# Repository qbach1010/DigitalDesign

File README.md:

## Digital Design Project

## 📝 Project Overview

Design a 3-bit signed (X) to 3-bit signed (Y) computer, which includes operations: add, subtract, multiply, and XOR. The user can select X, Y, and the operation to compute via physical switches. 

*   **EDA Tool:** KiCad 10.0
  
*   **Dimensions:** 120 x 180 mm
  
*   **Layer Count:** 2 layers
  
*   **Primary Logic:** Computes directly through discrete logic gates: AND (CD4081), OR (CD4071), and NOT (74HC04).
  
*   **Libraries Used:** Standard KiCad library.

### 📸 Schematics & Layout

---

## 🛠️ Key Hardware Features
The main functional blocks of the schematic include:

*   **Power Supply:** Uses a 7805 voltage regulator to accept 7 ~ 14 VDC, or just using 5VDC pin to power up the circuit and provide the logic HIGH.
  
*   **Adder:** A simple 3-bit to 3-bit adder using full adders.
  
*   **Two's Complement:** Changes the sign of the 3-bit number, utilizing the adder block to also perform subtraction.
  
*   **Multiplier:** Uses **Baugh-Wooley multiplication** for multiplying the signed 3-bit numbers.
  
*   **Sign Extend:** Due to the difference between the output of the multiply operation (6 bits) and all other operations (3 bits), sign-extension logic is added to make all final outputs a uniform 6 bits wide.

---

## 🔍 Editing the Design
To view or modify the hardware files:

1. Clone this repository to your local machine.

2. Open the main `.kicad_pro` project file in **KiCad 10.0**.

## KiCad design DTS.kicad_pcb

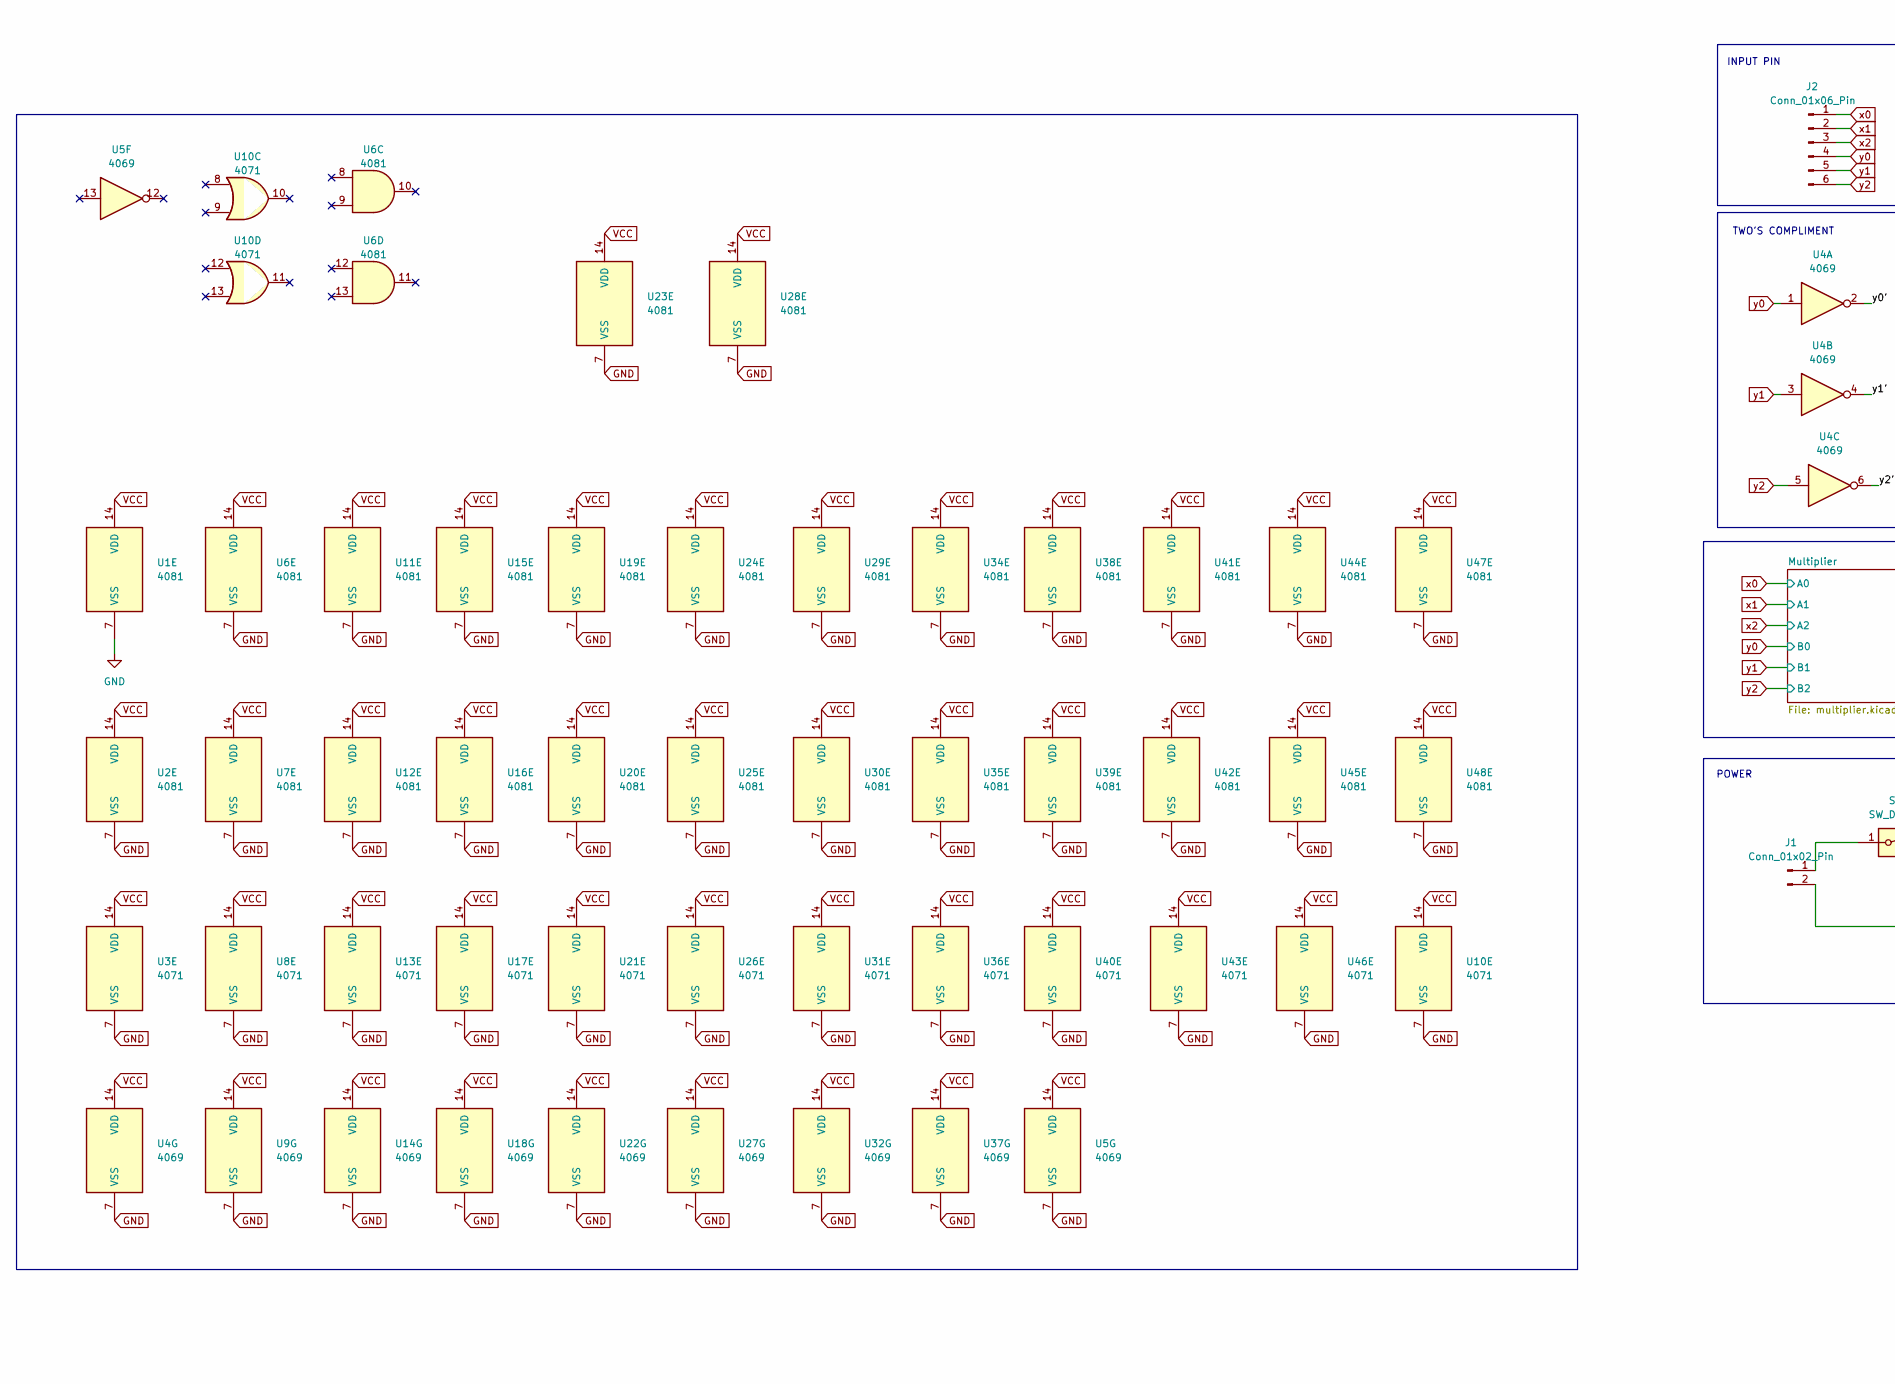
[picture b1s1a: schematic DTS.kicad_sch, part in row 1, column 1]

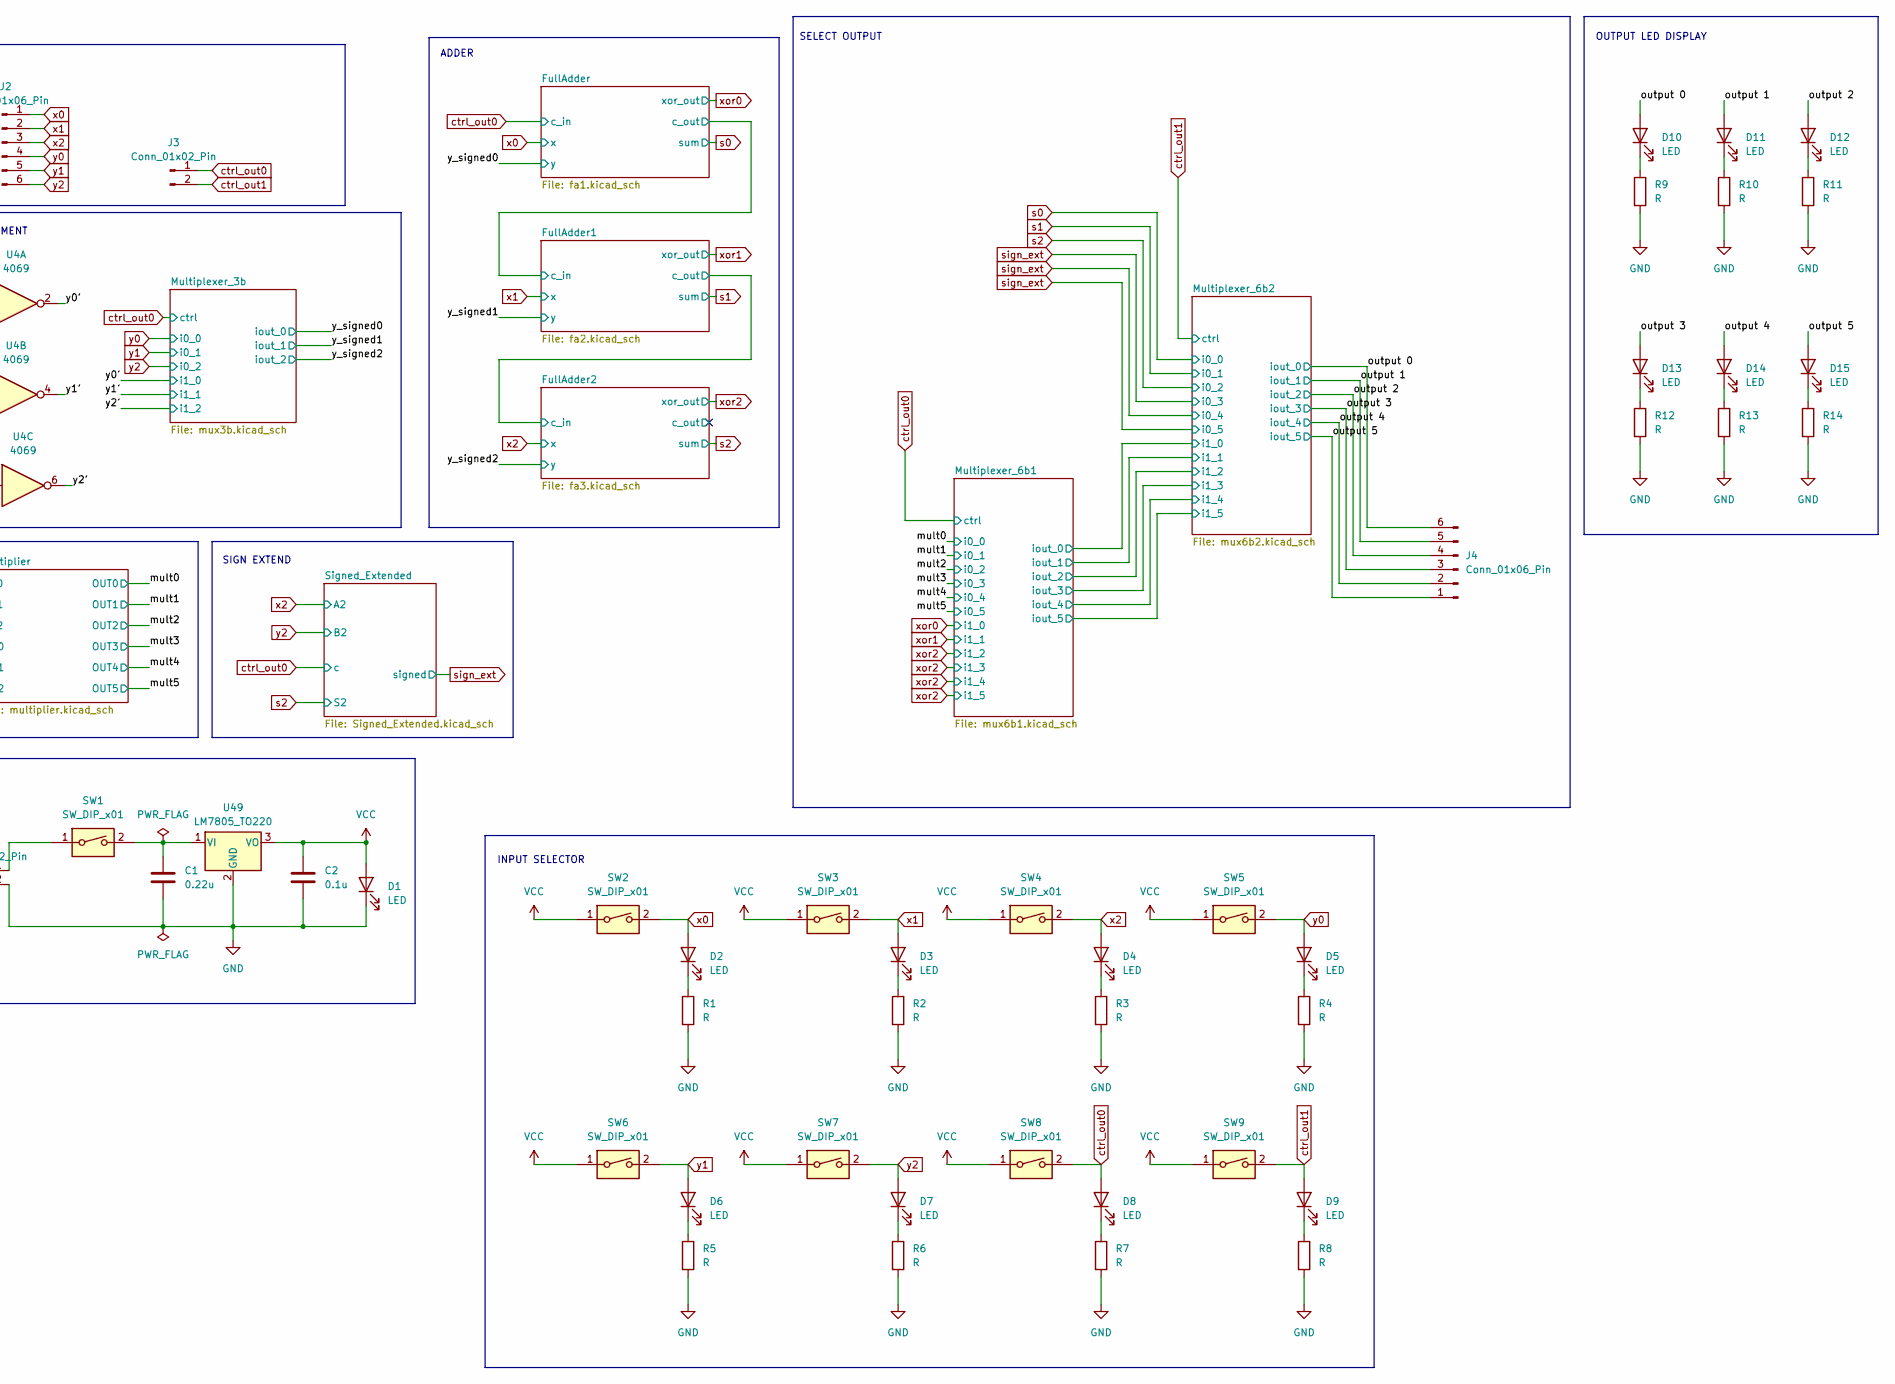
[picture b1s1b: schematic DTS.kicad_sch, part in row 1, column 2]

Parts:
C1: 0.22u; C_Radial_D6.3mm_H5.0mm_P2.50mm
C2: 0.1u; C_Radial_D6.3mm_H5.0mm_P2.50mm
D1, D2, D3, D4, D5, D6, D7, D8, D9, D10, D11, D12, D13, D14, D15: LED; PinHeader_1x02_P2.54mm_Vertical
J1, J3: Conn_01x02_Pin; PinHeader_1x02_P2.54mm_Vertical
J2, J4: Conn_01x06_Pin; PinHeader_1x06_P2.54mm_Vertical
R1, R2, R3, R4, R5, R6, R7, R8, R9, R10, R11, R12, R13, R14: R; PinHeader_1x02_P2.54mm_Vertical
SW1, SW2, SW3, SW4, SW5, SW6, SW7, SW8, SW9: SW_DIP_x01; PinHeader_1x03_P2.54mm_Vertical
U1, U2, U6, U7, U11, U12, U15, U16, U19, U20, U23, U24, U25, U28, U29, U30, U34, U35, U38, U39, U41, U42, U44, U45, U47, U48: 4081; CERDIP-14_W7.62mm_SideBrazed_LongPads_Socket
U3, U8, U10, U13, U17, U21, U26, U31, U36, U40, U43, U46: 4071; CERDIP-14_W7.62mm_SideBrazed_LongPads_Socket
U4, U5, U9, U14, U18, U22, U27, U32, U37: 4069; CERDIP-14_W7.62mm_SideBrazed_LongPads_Socket
U49: LM7805_TO220; TO-220-3_Vertical

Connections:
/output 0: D10.2 (A), J4.6; also elsewhere on the board
/output 1: D11.2 (A), J4.5; also elsewhere on the board
/output 2: D12.2 (A), J4.4; also elsewhere on the board
/output 3: D13.2 (A), J4.3; also elsewhere on the board
/output 4: D14.2 (A), J4.2; also elsewhere on the board
/output 5: D15.2 (A), J4.1; also elsewhere on the board
/y0': U4.2; also elsewhere on the board
/y1': U4.4; also elsewhere on the board
/y2': U4.6; also elsewhere on the board
GND: C1.2, C2.2, D1.1 (K), J1.2, R1.2, R2.2, R3.2, R4.2, R5.2, R6.2, R7.2, R8.2, R9.2, R10.2, R11.2, R12.2, R13.2, R14.2, U1.7 (VSS), U2.7 (VSS), U3.7 (VSS), U4.7 (VSS), U5.7 (VSS), U6.7 (VSS), U7.7 (VSS), U8.7 (VSS), U9.7 (VSS), U10.7 (VSS), U11.7 (VSS), U12.7 (VSS), U13.7 (VSS), U14.7 (VSS), U15.7 (VSS), U16.7 (VSS), U17.7 (VSS), U18.7 (VSS), U19.7 (VSS), U20.7 (VSS), U21.7 (VSS), U22.7 (VSS), U23.7 (VSS), U24.7 (VSS), U25.7 (VSS), U26.7 (VSS), U27.7 (VSS), U28.7 (VSS), U29.7 (VSS), U30.7 (VSS), U31.7 (VSS), U32.7 (VSS), U34.7 (VSS), U35.7 (VSS), U36.7 (VSS), U37.7 (VSS), U38.7 (VSS), U39.7 (VSS), U40.7 (VSS), U41.7 (VSS), U42.7 (VSS), U43.7 (VSS), U44.7 (VSS), U45.7 (VSS), U46.7 (VSS), U47.7 (VSS), U48.7 (VSS), U49.2 (GND); also elsewhere on the board
unnamed: D2.1 (K), R1.1
unnamed: D3.1 (K), R2.1
unnamed: D4.1 (K), R3.1
unnamed: D5.1 (K), R4.1
unnamed: D6.1 (K), R5.1
unnamed: D7.1 (K), R6.1
unnamed: D8.1 (K), R7.1
unnamed: D9.1 (K), R8.1
unnamed: D10.1 (K), R9.1
unnamed: D11.1 (K), R10.1
unnamed: D12.1 (K), R11.1
unnamed: D13.1 (K), R12.1
unnamed: D14.1 (K), R13.1
unnamed: D15.1 (K), R14.1
unnamed: J1.1, SW1.1
unnamed: C1.1, SW1.2, U49.1 (VI)
VCC: C2.1, D1.2 (A), SW2.1, SW3.1, SW4.1, SW5.1, SW6.1, SW7.1, SW8.1, SW9.1, U1.14 (VDD), U2.14 (VDD), U3.14 (VDD), U4.14 (VDD), U5.14 (VDD), U6.14 (VDD), U7.14 (VDD), U8.14 (VDD), U9.14 (VDD), U10.14 (VDD), U11.14 (VDD), U12.14 (VDD), U13.14 (VDD), U14.14 (VDD), U15.14 (VDD), U16.14 (VDD), U17.14 (VDD), U18.14 (VDD), U19.14 (VDD), U20.14 (VDD), U21.14 (VDD), U22.14 (VDD), U23.14 (VDD), U24.14 (VDD), U25.14 (VDD), U26.14 (VDD), U27.14 (VDD), U28.14 (VDD), U29.14 (VDD), U30.14 (VDD), U31.14 (VDD), U32.14 (VDD), U34.14 (VDD), U35.14 (VDD), U36.14 (VDD), U37.14 (VDD), U38.14 (VDD), U39.14 (VDD), U40.14 (VDD), U41.14 (VDD), U42.14 (VDD), U43.14 (VDD), U44.14 (VDD), U45.14 (VDD), U46.14 (VDD), U47.14 (VDD), U48.14 (VDD), U49.3 (VO); also elsewhere on the board
ctrl_out0: D8.2 (A), J3.1, SW8.2; also elsewhere on the board
ctrl_out1: D9.2 (A), J3.2, SW9.2; also elsewhere on the board
x0: D2.2 (A), J2.1, SW2.2; also elsewhere on the board
x1: D3.2 (A), J2.2, SW3.2; also elsewhere on the board
x2: D4.2 (A), J2.3, SW4.2; also elsewhere on the board
y0: D5.2 (A), J2.4, SW5.2, U4.1; also elsewhere on the board
y1: D6.2 (A), J2.5, SW6.2, U4.3; also elsewhere on the board
y2: D7.2 (A), J2.6, SW7.2, U4.5; also elsewhere on the board

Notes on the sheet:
ADDER
INPUT PIN
SIGN EXTEND
POWER
SELECT OUTPUT
OUTPUT LED DISPLAY
TWO'S COMPLIMENT
INPUT SELECTOR

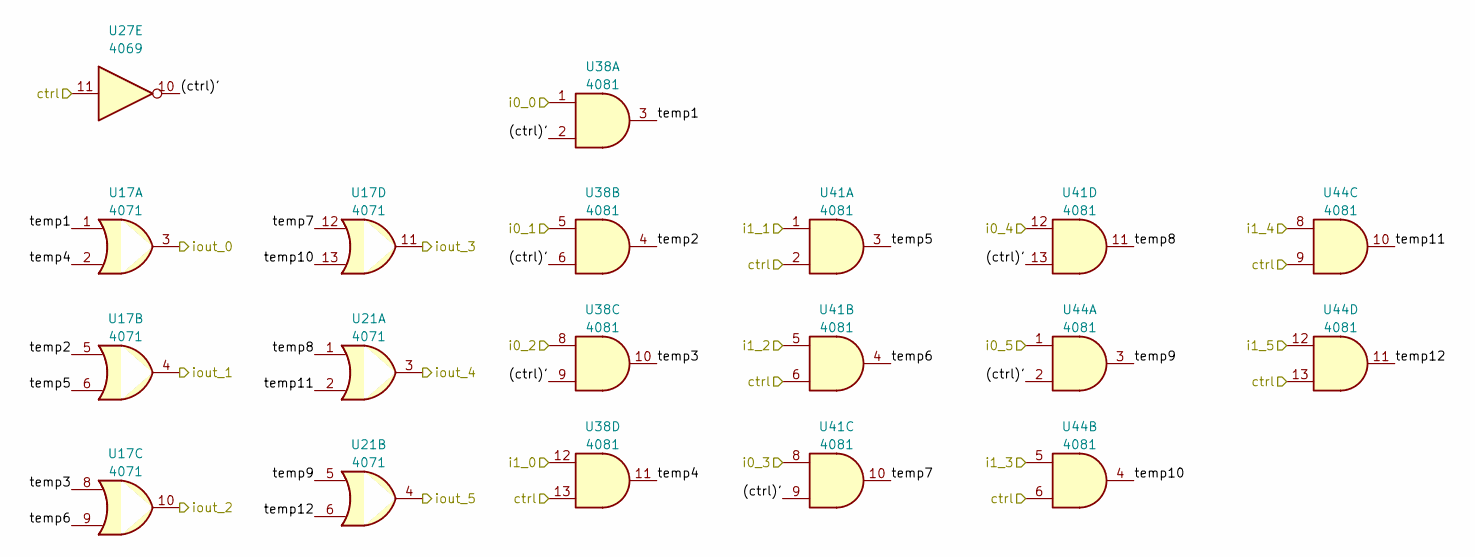
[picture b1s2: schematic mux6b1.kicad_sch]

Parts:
U17, U21: 4071; CERDIP-14_W7.62mm_SideBrazed_LongPads_Socket
U27: 4069; CERDIP-14_W7.62mm_SideBrazed_LongPads_Socket
U38, U41, U44: 4081; CERDIP-14_W7.62mm_SideBrazed_LongPads_Socket

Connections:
/Multiplexer_6b1/(ctrl)': U27.10, U38.2, U38.6, U38.9, U41.9, U41.13, U44.2
/Multiplexer_6b1/iout_0: U17.3; also elsewhere on the board
/Multiplexer_6b1/iout_1: U17.4; also elsewhere on the board
/Multiplexer_6b1/iout_2: U17.10; also elsewhere on the board
/Multiplexer_6b1/iout_3: U17.11; also elsewhere on the board
/Multiplexer_6b1/iout_4: U21.3; also elsewhere on the board
/Multiplexer_6b1/iout_5: U21.4; also elsewhere on the board
/Multiplexer_6b1/temp1: U17.1, U38.3
/Multiplexer_6b1/temp2: U17.5, U38.4
/Multiplexer_6b1/temp3: U17.8, U38.10
/Multiplexer_6b1/temp4: U17.2, U38.11
/Multiplexer_6b1/temp5: U17.6, U41.3
/Multiplexer_6b1/temp6: U17.9, U41.4
/Multiplexer_6b1/temp7: U17.12, U41.10
/Multiplexer_6b1/temp8: U21.1, U41.11
/Multiplexer_6b1/temp9: U21.5, U44.3
/Multiplexer_6b1/temp10: U17.13, U44.4
/Multiplexer_6b1/temp11: U21.2, U44.10
/Multiplexer_6b1/temp12: U21.6, U44.11
/mult0: U38.1; also elsewhere on the board
/mult1: U38.5; also elsewhere on the board
/mult2: U38.8; also elsewhere on the board
/mult3: U41.8; also elsewhere on the board
/mult4: U41.12; also elsewhere on the board
/mult5: U44.1; also elsewhere on the board
ctrl_out0: U27.11, U38.13, U41.2, U41.6, U44.6, U44.9, U44.13; also elsewhere on the board
xor0: U38.12; also elsewhere on the board
xor1: U41.1; also elsewhere on the board
xor2: U41.5, U44.5, U44.8, U44.12; also elsewhere on the board

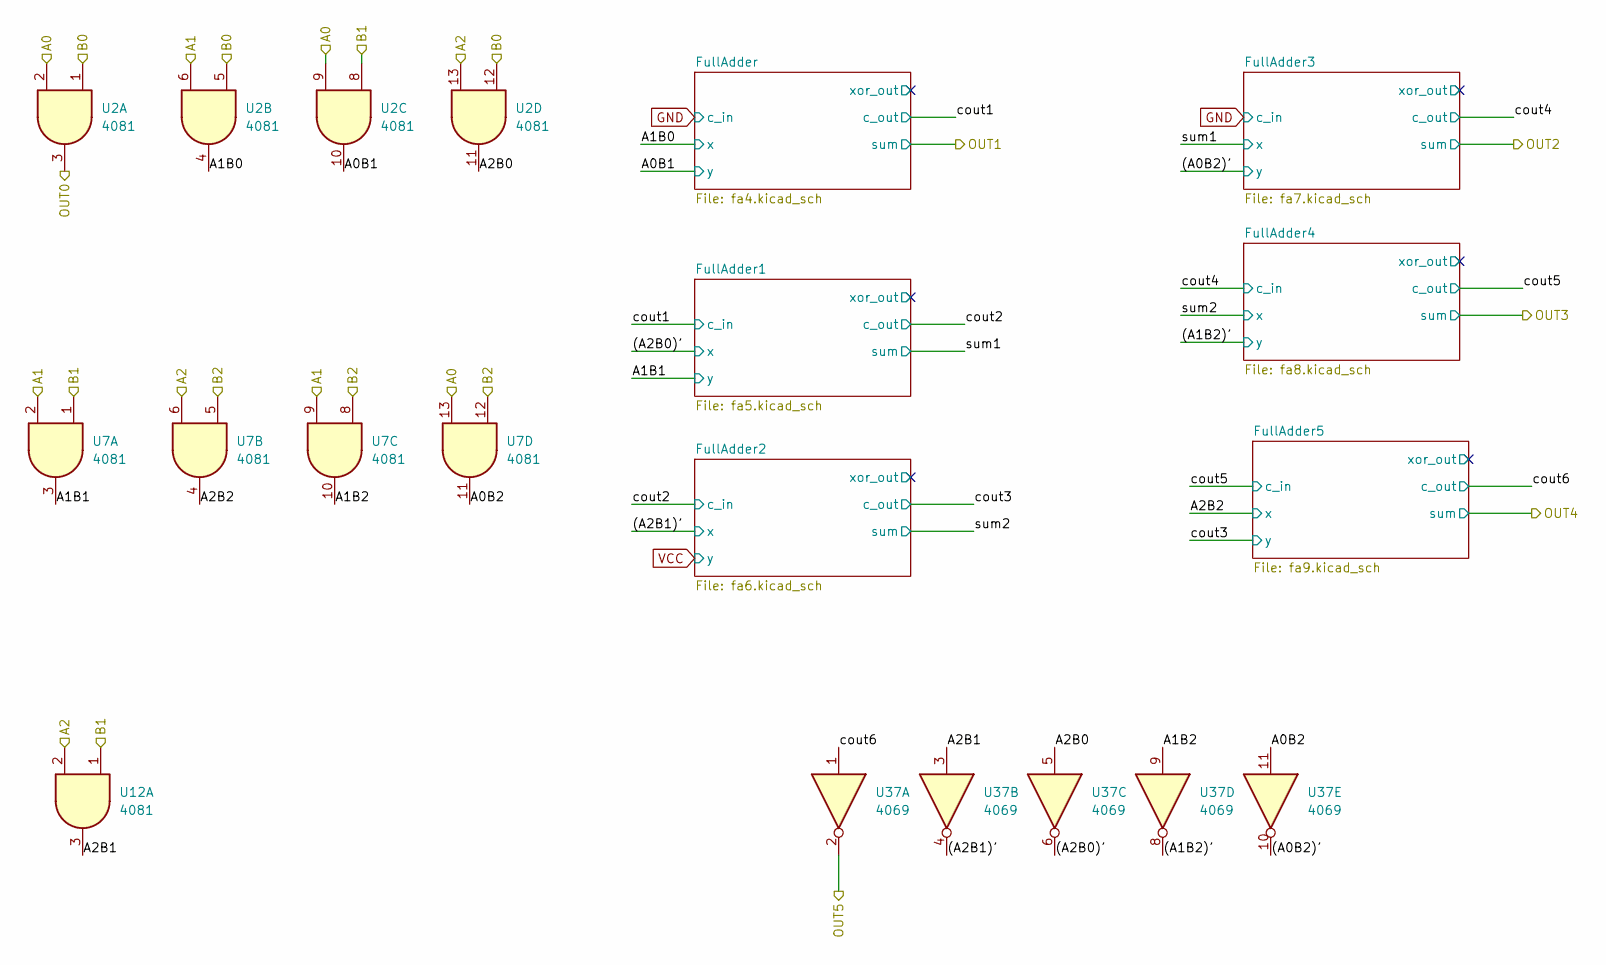
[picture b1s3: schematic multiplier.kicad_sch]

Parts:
U2, U7, U12: 4081; CERDIP-14_W7.62mm_SideBrazed_LongPads_Socket
U37: 4069; CERDIP-14_W7.62mm_SideBrazed_LongPads_Socket

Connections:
/Multiplier/(A0B2)': U37.10; also elsewhere on the board
/Multiplier/(A1B2)': U37.8; also elsewhere on the board
/Multiplier/(A2B0)': U37.6; also elsewhere on the board
/Multiplier/(A2B1)': U37.4; also elsewhere on the board
/Multiplier/A0B1: U2.10; also elsewhere on the board
/Multiplier/A0B2: U7.11, U37.11
/Multiplier/A1B0: U2.4; also elsewhere on the board
/Multiplier/A1B1: U7.3; also elsewhere on the board
/Multiplier/A1B2: U7.10, U37.9
/Multiplier/A2B0: U2.11, U37.5
/Multiplier/A2B1: U12.3, U37.3
/Multiplier/A2B2: U7.4; also elsewhere on the board
/Multiplier/cout6: U37.1; also elsewhere on the board
/mult0: U2.3; also elsewhere on the board
/mult5: U37.2; also elsewhere on the board
x0: U2.2, U2.9, U7.13; also elsewhere on the board
x1: U2.6, U7.2, U7.9; also elsewhere on the board
x2: U2.13, U7.6, U12.2; also elsewhere on the board
y0: U2.1, U2.5, U2.12; also elsewhere on the board
y1: U2.8, U7.1, U12.1; also elsewhere on the board
y2: U7.5, U7.8, U7.12; also elsewhere on the board

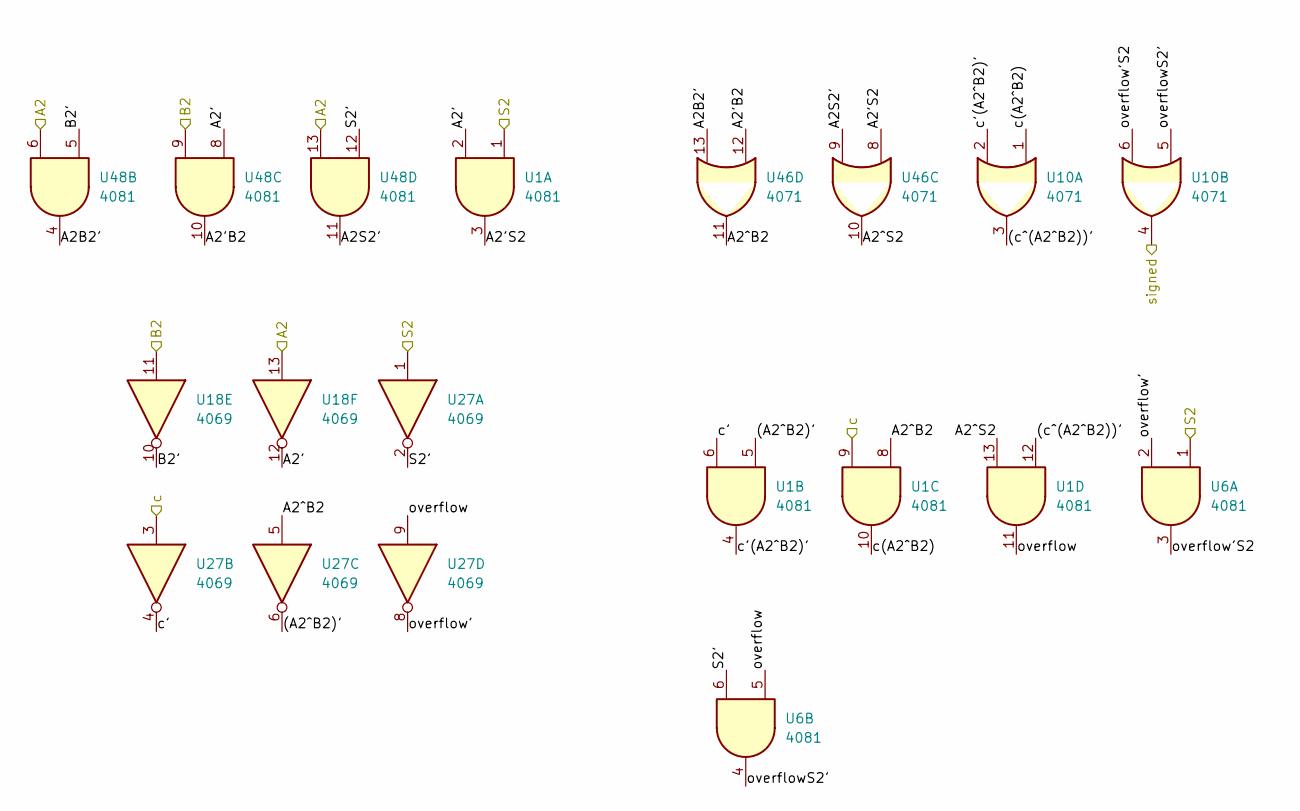
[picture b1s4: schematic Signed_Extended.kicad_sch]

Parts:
U1, U6, U48: 4081; CERDIP-14_W7.62mm_SideBrazed_LongPads_Socket
U10, U46: 4071; CERDIP-14_W7.62mm_SideBrazed_LongPads_Socket
U18, U27: 4069; CERDIP-14_W7.62mm_SideBrazed_LongPads_Socket

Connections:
/Signed_Extended/(A2^B2)': U1.5, U27.6
/Signed_Extended/(c^(A2^B2))': U1.12, U10.3
/Signed_Extended/A2': U1.2, U18.12, U48.8
/Signed_Extended/A2'B2: U46.12, U48.10
/Signed_Extended/A2'S2: U1.3, U46.8
/Signed_Extended/A2B2': U46.13, U48.4
/Signed_Extended/A2S2': U46.9, U48.11
/Signed_Extended/A2^B2: U1.8, U27.5, U46.11
/Signed_Extended/A2^S2: U1.13, U46.10
/Signed_Extended/B2': U18.10, U48.5
/Signed_Extended/S2': U6.6, U27.2, U48.12
/Signed_Extended/c': U1.6, U27.4
/Signed_Extended/c'(A2^B2)': U1.4, U10.2
/Signed_Extended/c(A2^B2): U1.10, U10.1
/Signed_Extended/overflow: U1.11, U6.5, U27.9
/Signed_Extended/overflow': U6.2, U27.8
/Signed_Extended/overflow'S2: U6.3, U10.6
/Signed_Extended/overflowS2': U6.4, U10.5
ctrl_out0: U1.9, U27.3; also elsewhere on the board
s2: U1.1, U6.1, U27.1; also elsewhere on the board
sign_ext: U10.4; also elsewhere on the board
x2: U18.13, U48.6, U48.13; also elsewhere on the board
y2: U18.11, U48.9; also elsewhere on the board

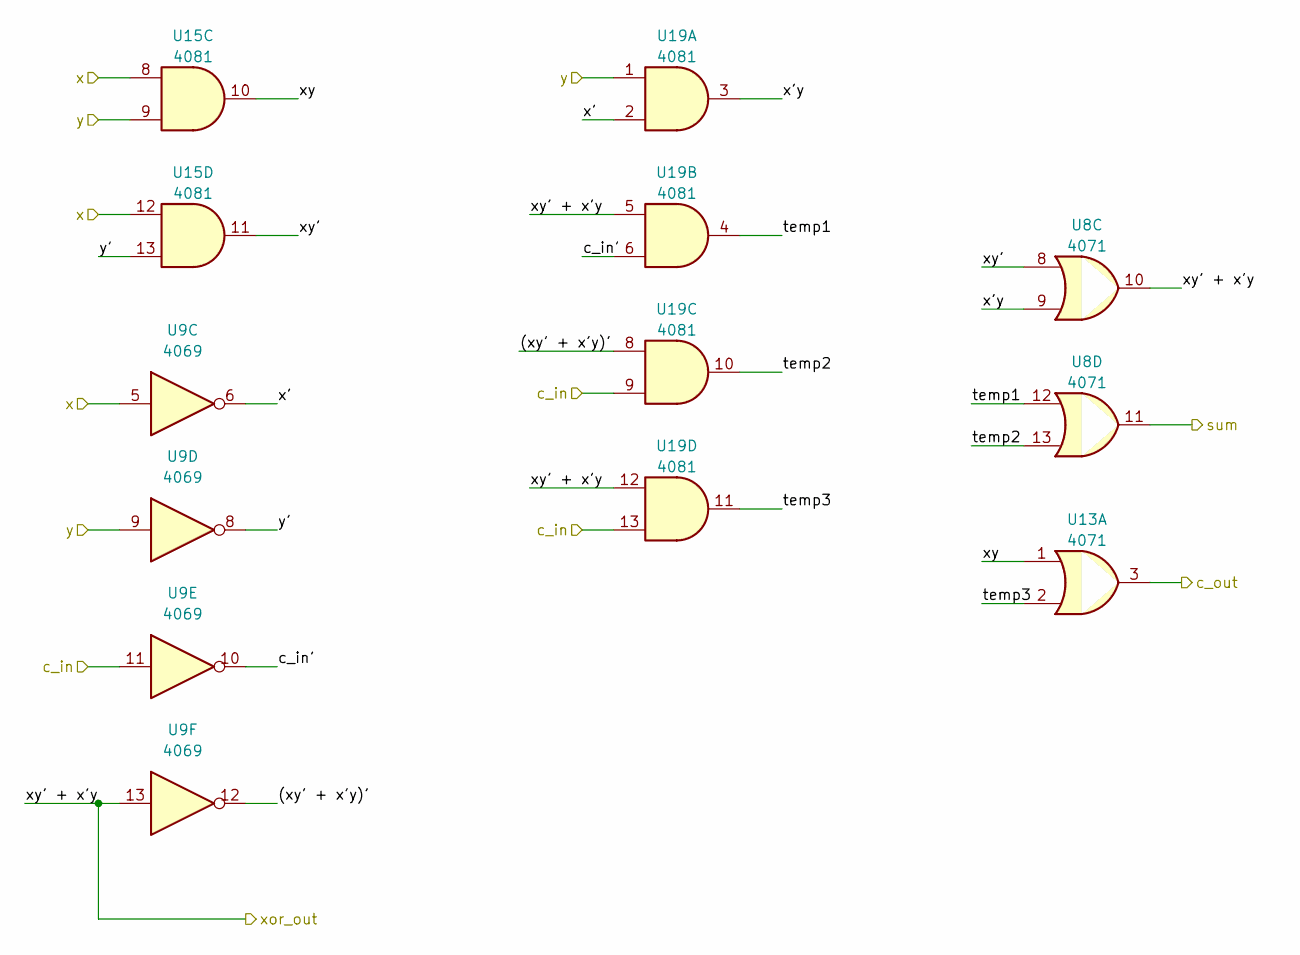
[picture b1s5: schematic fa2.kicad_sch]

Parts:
U8, U13: 4071; CERDIP-14_W7.62mm_SideBrazed_LongPads_Socket
U9: 4069; CERDIP-14_W7.62mm_SideBrazed_LongPads_Socket
U15, U19: 4081; CERDIP-14_W7.62mm_SideBrazed_LongPads_Socket

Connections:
/FullAdder1/(xy' + x'y)': U9.12, U19.8
/FullAdder1/c_in': U9.10, U19.6
/FullAdder1/c_out: U13.3; also elsewhere on the board
/FullAdder1/temp1: U8.12, U19.4
/FullAdder1/temp2: U8.13, U19.10
/FullAdder1/temp3: U13.2, U19.11
/FullAdder1/x': U9.6, U19.2
/FullAdder1/x'y: U8.9, U19.3
/FullAdder1/xy: U13.1, U15.10
/FullAdder1/xy': U8.8, U15.11
/FullAdder1/y': U9.8, U15.13
/FullAdder/c_out: U9.11, U19.9, U19.13; also elsewhere on the board
/y_signed1: U9.9, U15.9, U19.1; also elsewhere on the board
s1: U8.11; also elsewhere on the board
x1: U9.5, U15.8, U15.12; also elsewhere on the board
xor1: U8.10, U9.13, U19.5, U19.12; also elsewhere on the board

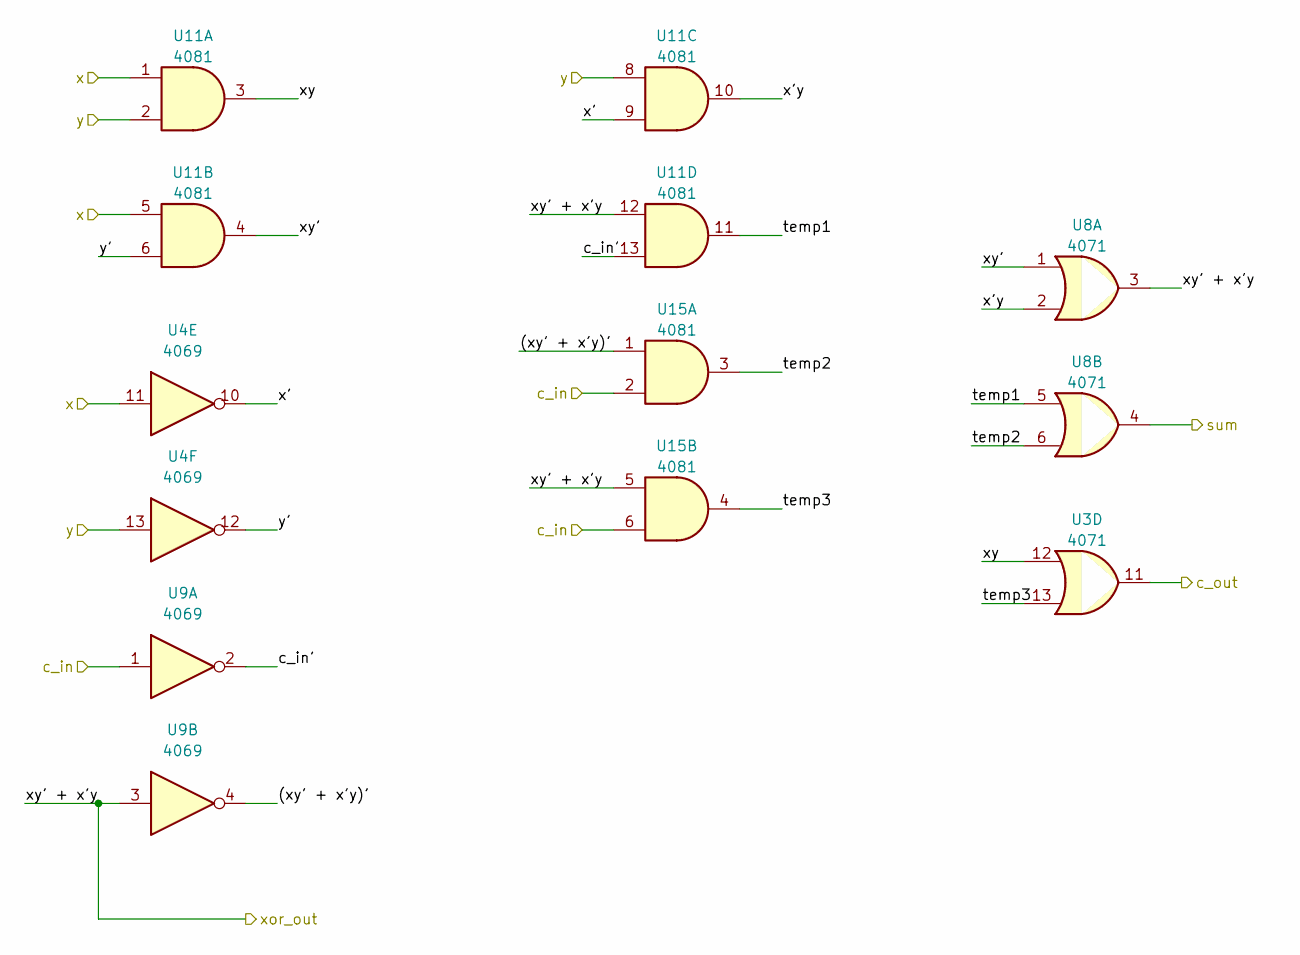
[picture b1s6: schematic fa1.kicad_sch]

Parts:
U3, U8: 4071; CERDIP-14_W7.62mm_SideBrazed_LongPads_Socket
U4, U9: 4069; CERDIP-14_W7.62mm_SideBrazed_LongPads_Socket
U11, U15: 4081; CERDIP-14_W7.62mm_SideBrazed_LongPads_Socket

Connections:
/FullAdder/(xy' + x'y)': U9.4, U15.1
/FullAdder/c_in': U9.2, U11.13
/FullAdder/c_out: U3.11; also elsewhere on the board
/FullAdder/temp1: U8.5, U11.11
/FullAdder/temp2: U8.6, U15.3
/FullAdder/temp3: U3.13, U15.4
/FullAdder/x': U4.10, U11.9
/FullAdder/x'y: U8.2, U11.10
/FullAdder/xy: U3.12, U11.3
/FullAdder/xy': U8.1, U11.4
/FullAdder/y': U4.12, U11.6
/y_signed0: U4.13, U11.2, U11.8; also elsewhere on the board
ctrl_out0: U9.1, U15.2, U15.6; also elsewhere on the board
s0: U8.4; also elsewhere on the board
x0: U4.11, U11.1, U11.5; also elsewhere on the board
xor0: U8.3, U9.3, U11.12, U15.5; also elsewhere on the board

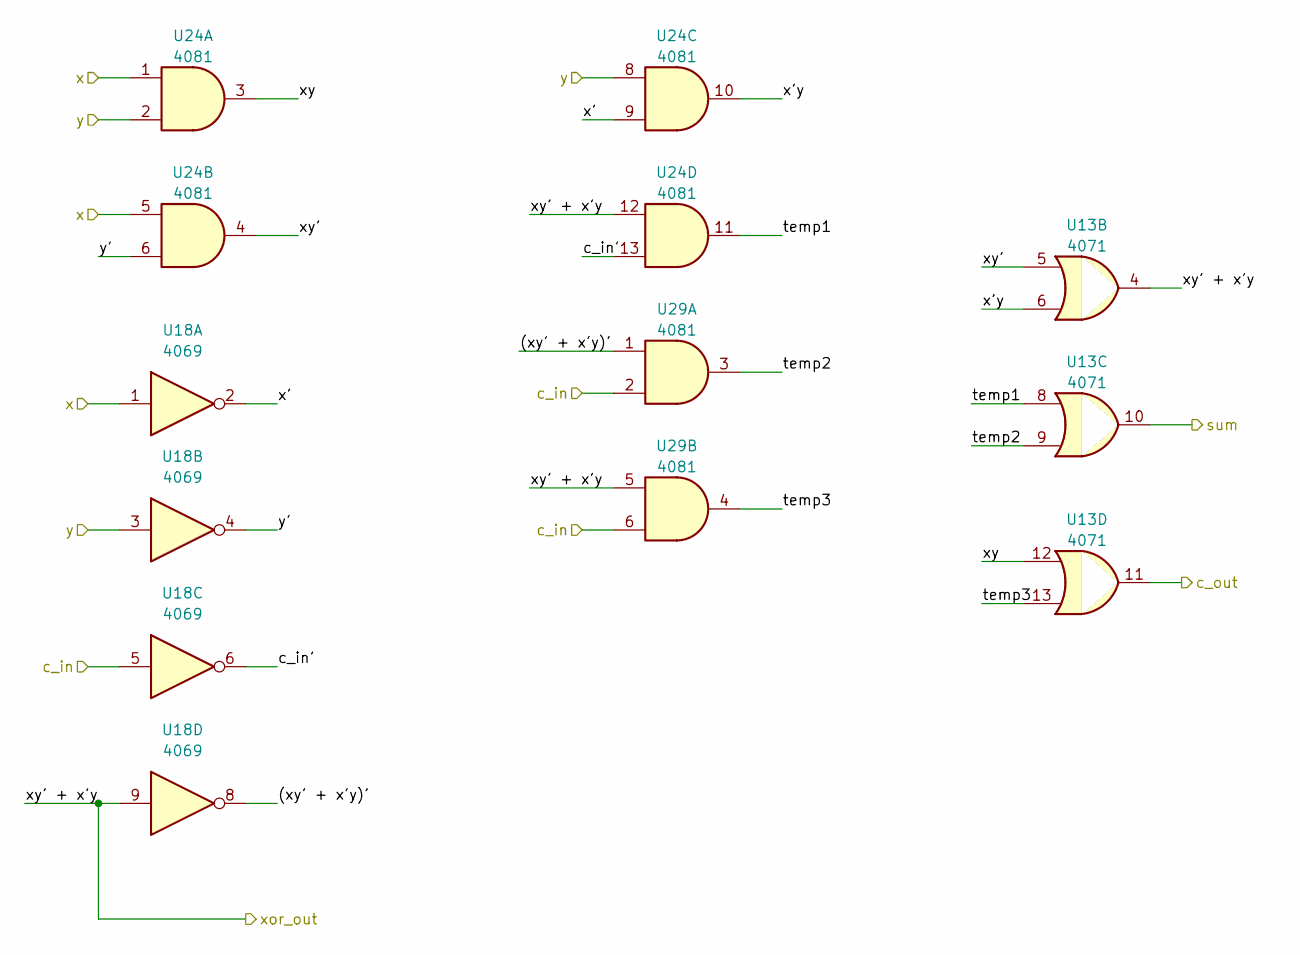
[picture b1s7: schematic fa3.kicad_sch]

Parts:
U13: 4071; CERDIP-14_W7.62mm_SideBrazed_LongPads_Socket
U18: 4069; CERDIP-14_W7.62mm_SideBrazed_LongPads_Socket
U24, U29: 4081; CERDIP-14_W7.62mm_SideBrazed_LongPads_Socket

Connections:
/FullAdder1/c_out: U18.5, U29.2, U29.6; also elsewhere on the board
/FullAdder2/(xy' + x'y)': U18.8, U29.1
/FullAdder2/c_in': U18.6, U24.13
/FullAdder2/c_out: U13.11
/FullAdder2/temp1: U13.8, U24.11
/FullAdder2/temp2: U13.9, U29.3
/FullAdder2/temp3: U13.13, U29.4
/FullAdder2/x': U18.2, U24.9
/FullAdder2/x'y: U13.6, U24.10
/FullAdder2/xy: U13.12, U24.3
/FullAdder2/xy': U13.5, U24.4
/FullAdder2/y': U18.4, U24.6
/y_signed2: U18.3, U24.2, U24.8; also elsewhere on the board
s2: U13.10; also elsewhere on the board
x2: U18.1, U24.1, U24.5; also elsewhere on the board
xor2: U13.4, U18.9, U24.12, U29.5; also elsewhere on the board

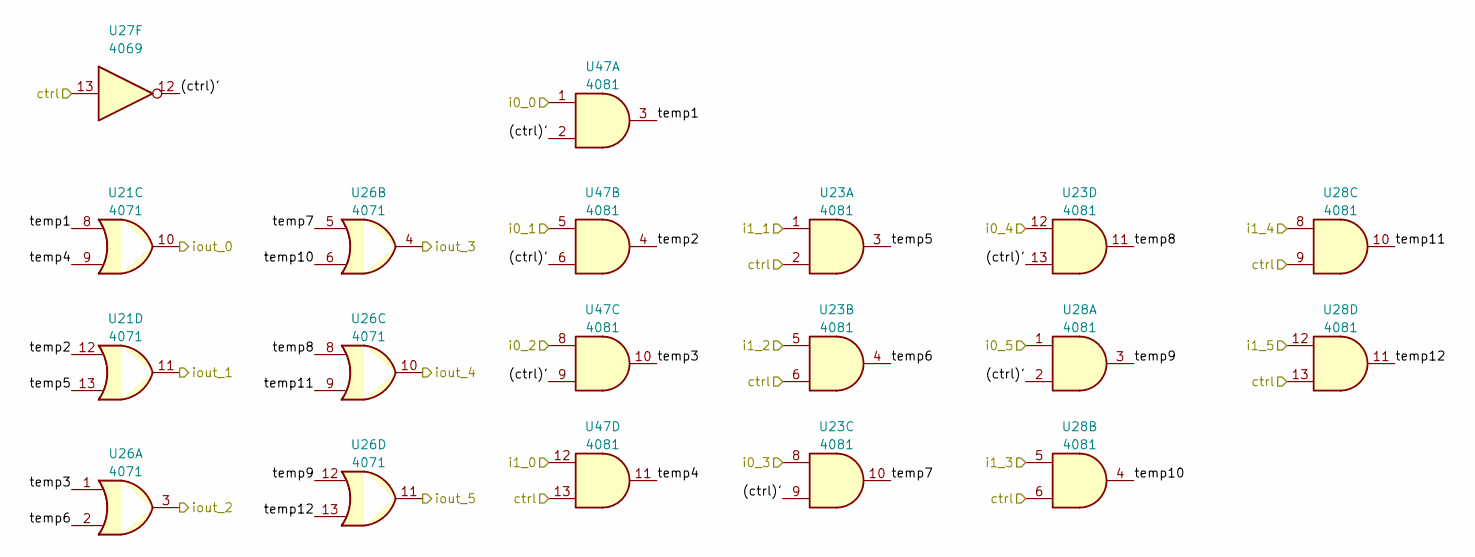
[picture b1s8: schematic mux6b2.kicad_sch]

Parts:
U21, U26: 4071; CERDIP-14_W7.62mm_SideBrazed_LongPads_Socket
U23, U28, U47: 4081; CERDIP-14_W7.62mm_SideBrazed_LongPads_Socket
U27: 4069; CERDIP-14_W7.62mm_SideBrazed_LongPads_Socket

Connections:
/Multiplexer_6b1/iout_0: U47.12; also elsewhere on the board
/Multiplexer_6b1/iout_1: U23.1; also elsewhere on the board
/Multiplexer_6b1/iout_2: U23.5; also elsewhere on the board
/Multiplexer_6b1/iout_3: U28.5; also elsewhere on the board
/Multiplexer_6b1/iout_4: U28.8; also elsewhere on the board
/Multiplexer_6b1/iout_5: U28.12; also elsewhere on the board
/Multiplexer_6b2/(ctrl)': U23.9, U23.13, U27.12, U28.2, U47.2, U47.6, U47.9
/Multiplexer_6b2/temp1: U21.8, U47.3
/Multiplexer_6b2/temp2: U21.12, U47.4
/Multiplexer_6b2/temp3: U26.1, U47.10
/Multiplexer_6b2/temp4: U21.9, U47.11
/Multiplexer_6b2/temp5: U21.13, U23.3
/Multiplexer_6b2/temp6: U23.4, U26.2
/Multiplexer_6b2/temp7: U23.10, U26.5
/Multiplexer_6b2/temp8: U23.11, U26.8
/Multiplexer_6b2/temp9: U26.12, U28.3
/Multiplexer_6b2/temp10: U26.6, U28.4
/Multiplexer_6b2/temp11: U26.9, U28.10
/Multiplexer_6b2/temp12: U26.13, U28.11
/output 0: U21.10; also elsewhere on the board
/output 1: U21.11; also elsewhere on the board
/output 2: U26.3; also elsewhere on the board
/output 3: U26.4; also elsewhere on the board
/output 4: U26.10; also elsewhere on the board
/output 5: U26.11; also elsewhere on the board
ctrl_out1: U23.2, U23.6, U27.13, U28.6, U28.9, U28.13, U47.13; also elsewhere on the board
s0: U47.1; also elsewhere on the board
s1: U47.5; also elsewhere on the board
s2: U47.8; also elsewhere on the board
sign_ext: U23.8, U23.12, U28.1; also elsewhere on the board

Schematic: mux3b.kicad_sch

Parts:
U3: 4071; CERDIP-14_W7.62mm_SideBrazed_LongPads_Socket
U4: 4069; CERDIP-14_W7.62mm_SideBrazed_LongPads_Socket
U29, U34: 4081; CERDIP-14_W7.62mm_SideBrazed_LongPads_Socket

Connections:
/Multiplexer_3b/(ctrl)': U4.8, U34.2, U34.9, U34.13
/Multiplexer_3b/temp1: U3.1, U34.10
/Multiplexer_3b/temp2: U3.5, U34.11
/Multiplexer_3b/temp3: U3.8, U34.3
/Multiplexer_3b/temp4: U3.2, U34.4
/Multiplexer_3b/temp5: U3.6, U29.10
/Multiplexer_3b/temp6: U3.9, U29.11
/y0': U34.5; also elsewhere on the board
/y1': U29.8; also elsewhere on the board
/y2': U29.12; also elsewhere on the board
/y_signed0: U3.3; also elsewhere on the board
/y_signed1: U3.4; also elsewhere on the board
/y_signed2: U3.10; also elsewhere on the board
ctrl_out0: U4.9, U29.9, U29.13, U34.6; also elsewhere on the board
y0: U34.8; also elsewhere on the board
y1: U34.12; also elsewhere on the board
y2: U34.1; also elsewhere on the board

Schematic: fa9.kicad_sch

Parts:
U5: 4069; CERDIP-14_W7.62mm_SideBrazed_LongPads_Socket
U42, U45, U48: 4081; CERDIP-14_W7.62mm_SideBrazed_LongPads_Socket
U43, U46: 4071; CERDIP-14_W7.62mm_SideBrazed_LongPads_Socket

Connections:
/Multiplier/A2B2: U5.3, U42.1, U45.1; also elsewhere on the board
/Multiplier/FullAdder5/(xy' + x'y)': U5.10, U45.12
/Multiplier/FullAdder5/c_in': U5.8, U45.9
/Multiplier/FullAdder5/temp1: U45.10, U46.1
/Multiplier/FullAdder5/temp2: U45.11, U46.2
/Multiplier/FullAdder5/temp3: U46.6, U48.3
/Multiplier/FullAdder5/x': U5.4, U45.6
/Multiplier/FullAdder5/x'y: U43.13, U45.4
/Multiplier/FullAdder5/xy: U42.3, U46.5
/Multiplier/FullAdder5/xy': U43.12, U45.3
/Multiplier/FullAdder5/xy' + x'y: U5.11, U43.11, U45.8, U48.1
/Multiplier/FullAdder5/y': U5.6, U45.2
/Multiplier/cout3: U5.5, U42.2, U45.5; also elsewhere on the board
/Multiplier/cout5: U5.9, U45.13, U48.2; also elsewhere on the board
/Multiplier/cout6: U46.4; also elsewhere on the board
/mult4: U46.3; also elsewhere on the board

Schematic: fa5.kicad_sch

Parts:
U14, U22: 4069; CERDIP-14_W7.62mm_SideBrazed_LongPads_Socket
U16, U20, U25: 4081; CERDIP-14_W7.62mm_SideBrazed_LongPads_Socket
U31, U36: 4071; CERDIP-14_W7.62mm_SideBrazed_LongPads_Socket

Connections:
/Multiplier/(A2B0)': U16.1, U20.1, U22.1; also elsewhere on the board
/Multiplier/A1B1: U14.9, U16.2, U20.5; also elsewhere on the board
/Multiplier/FullAdder1/(xy' + x'y)': U14.12, U20.12
/Multiplier/FullAdder1/c_in': U14.10, U20.9
/Multiplier/FullAdder1/temp1: U20.10, U36.5
/Multiplier/FullAdder1/temp2: U20.11, U36.6
/Multiplier/FullAdder1/temp3: U25.3, U31.13
/Multiplier/FullAdder1/x': U20.6, U22.2
/Multiplier/FullAdder1/x'y: U20.4, U36.2
/Multiplier/FullAdder1/xy: U16.3, U31.12
/Multiplier/FullAdder1/xy': U20.3, U36.1
/Multiplier/FullAdder1/xy' + x'y: U14.13, U20.8, U25.1, U36.3
/Multiplier/FullAdder1/y': U14.8, U20.2
/Multiplier/cout1: U14.11, U20.13, U25.2; also elsewhere on the board
/Multiplier/cout2: U31.11; also elsewhere on the board
/Multiplier/sum1: U36.4; also elsewhere on the board
